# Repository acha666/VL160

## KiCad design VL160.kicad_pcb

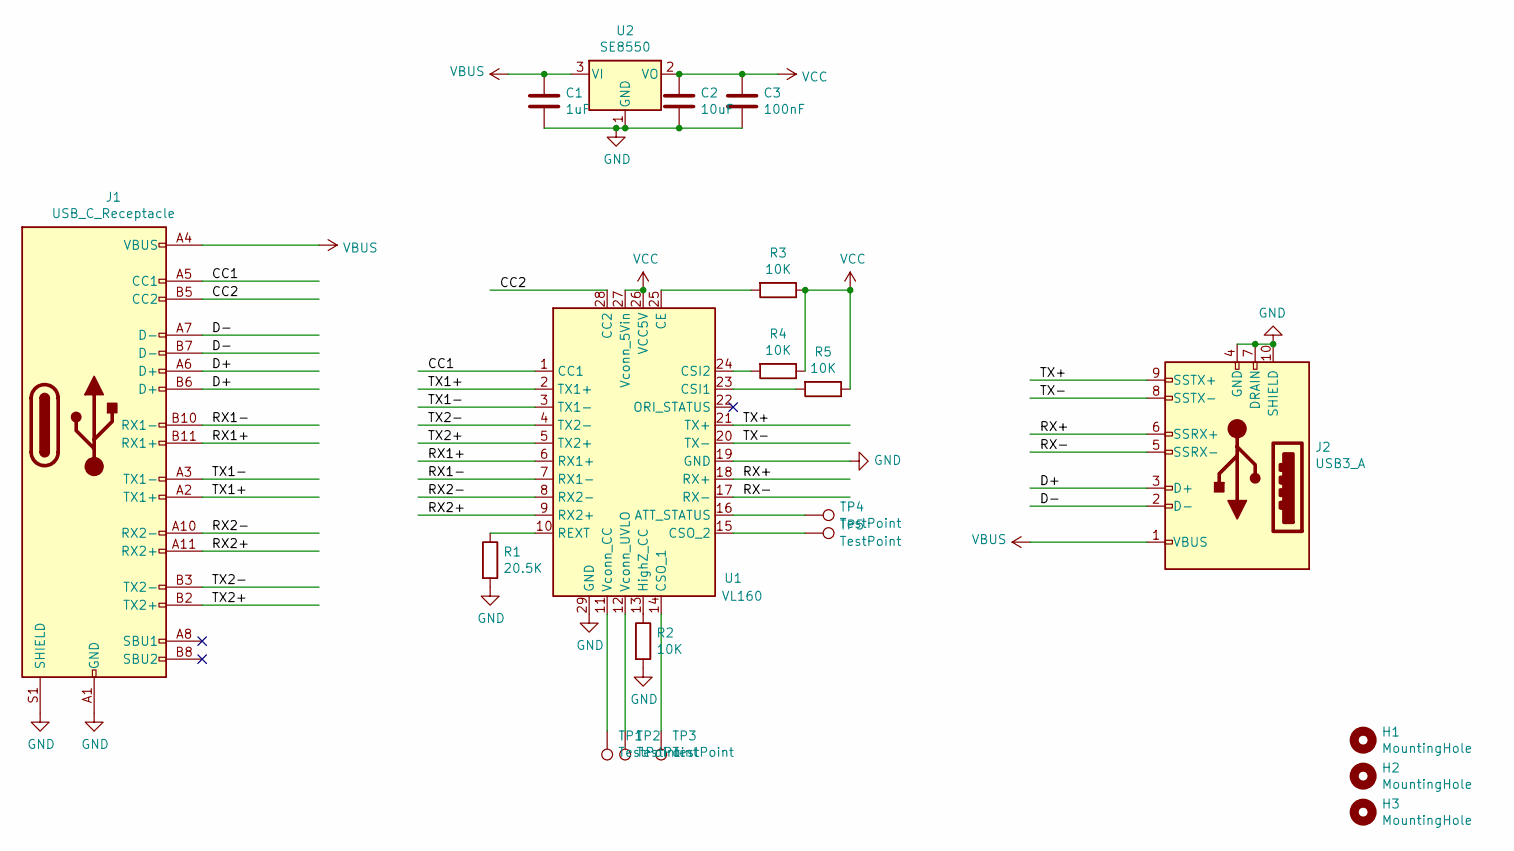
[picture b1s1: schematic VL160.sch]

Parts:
C1: 1uF; C_0603_1608Metric
C2: 10uF; C_0603_1608Metric
C3: 100nF; C_0603_1608Metric
H1, H2, H3: MountingHole; Hole_1.152mm_JLCSMT
J1: USB_C_Receptacle; USB_C_Receptacle_Amphenol_12401548E4-2A
J2: USB3_A; USB-A-SMD_U231-091N-4BLRA00-S-1
R1: 20.5K; R_0603_1608Metric
R2, R3, R4, R5: 10K; R_0603_1608Metric
TP1, TP2, TP3, TP4, TP5: TestPoint; TestPoint_Pad_D0.7mm
U1: VL160; WQFN-28_L4.5-W3.5-H0.8-P0.4
U2: SE8550; SOT-23

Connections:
/CC1: J1.A5 (CC1), U1.1 (CC1)
/CC2: J1.B5 (CC2), U1.28 (CC2)
/D+: J1.A6 (D+), J1.B6 (D+), J2.3 (D+)
/D-: J1.A7 (D-), J1.B7 (D-), J2.2 (D-)
/RX1+: J1.B11 (RX1+), U1.6 (RX1+)
/RX1-: J1.B10 (RX1-), U1.7 (RX1-)
/RX2+: J1.A11 (RX2+), U1.9 (RX2+)
/RX2-: J1.A10 (RX2-), U1.8 (RX2-)
/RX+: J2.6 (SSRX+), U1.18 (RX+)
/RX-: J2.5 (SSRX-), U1.17 (RX-)
/TX1+: J1.A2 (TX1+), U1.2 (TX1+)
/TX1-: J1.A3 (TX1-), U1.3 (TX1-)
/TX2+: J1.B2 (TX2+), U1.5 (TX2+)
/TX2-: J1.B3 (TX2-), U1.4 (TX2-)
/TX+: J2.9 (SSTX+), U1.21 (TX+)
/TX-: J2.8 (SSTX-), U1.20 (TX-)
GND: C1.2, C2.2, C3.2, J1.A1 (GND), J1.A12 (GND), J1.B1 (GND), J1.B12 (GND), J1.S1 (SHIELD), J2.4 (GND), J2.7 (DRAIN), J2.10 (SHIELD), R1.2, R2.2, U1.19 (GND), U1.29 (GND), U2.1 (GND)
unnamed: R1.1, U1.10 (REXT)
unnamed: R2.1, U1.13 (HighZ_CC)
unnamed: R3.2, U1.25 (CE)
unnamed: R4.2, U1.24 (CSI2)
unnamed: R5.2, U1.23 (CSI1)
unnamed: TP1.1, U1.11 (Vconn_CC)
unnamed: TP2.1, U1.12 (Vconn_UVLO)
unnamed: TP3.1, U1.14 (CSO_1)
unnamed: TP4.1, U1.16 (ATT_STATUS)
unnamed: TP5.1, U1.15 (CSO_2)
VBUS: C1.1, J1.A4 (VBUS), J1.A9 (VBUS), J1.B4 (VBUS), J1.B9 (VBUS), J2.1 (VBUS), U2.3 (VI)
VCC: C2.1, C3.1, R3.1, R4.1, R5.1, U1.26 (VCC5V), U1.27 (Vconn_5Vin), U2.2 (VO)

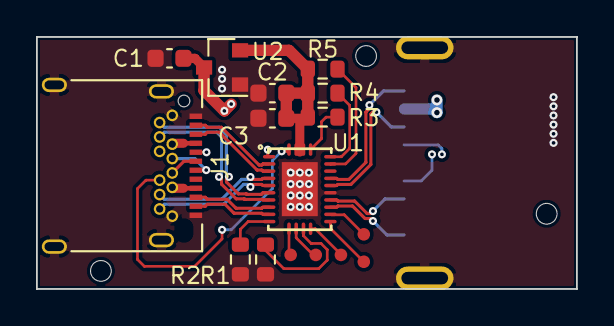
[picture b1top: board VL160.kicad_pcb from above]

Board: 4 copper layers, 30.0 x 14.0 mm, 20 parts (1 on the bottom side), 29 nets.

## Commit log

2022-01-05 Sync 2022/01/05 周三 16:51:25.41
2022-01-07 Sync 2022/01/07 周五 16:48:22.07
2022-01-11 Sync 2022/01/11 周二 21:14:02.89
2022-01-19 Sync 2022/01/19 周三 11:41:49.34
2022-02-13 Sync 2022/02/13 周日 21:51:31.67
